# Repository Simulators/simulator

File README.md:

# simulator
The Liverpool Ringing Simulator Project

<b>The Type 1 simulator is no longer under active development. The repository for the Type 2 simulator is at https://github.com/Simulators/simulator-type2, and you should start there if you are building a new simulator.</b>

Here you will find archived all the resources for building the Liverpool Ringing Simulator Project's original (Type 1) simulator interfaces and sensor heads, including:
* Hardware & Software Manuals
* Firmware Source Code
* Eagle PCB Designs
* PCB Fabrication Gerber Files

If you didn't get here from http://www.simulators.org.uk/, you might want to go and look at that, too.

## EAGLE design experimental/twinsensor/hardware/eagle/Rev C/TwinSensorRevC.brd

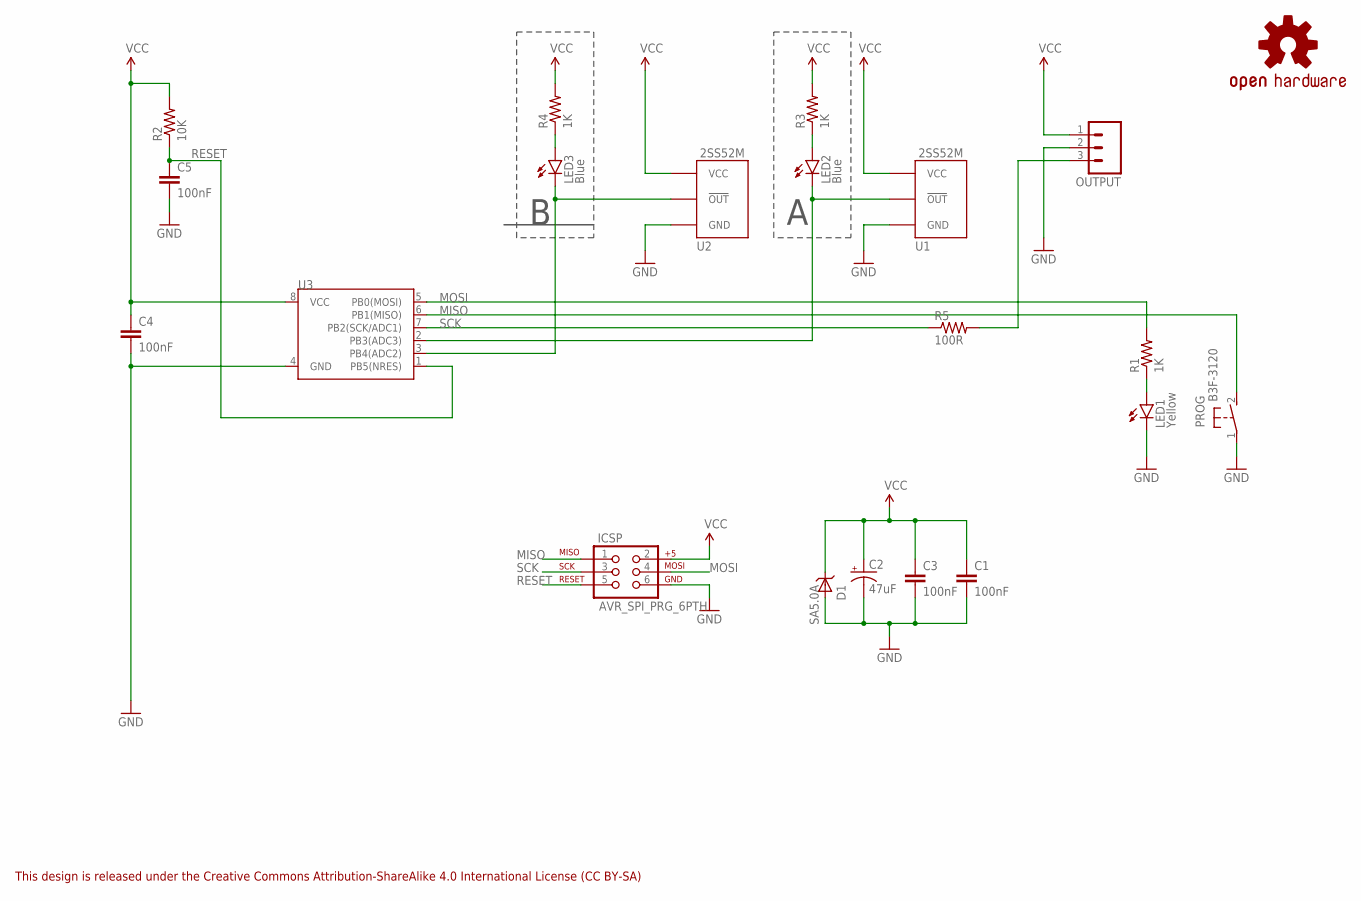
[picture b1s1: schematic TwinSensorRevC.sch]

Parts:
C1, C3, C4, C5: 100nF; CAP-PTH-SMALL
C2: 47uF; CPOL-RADIAL-100UF-25V
D1: SA5.0A; DO41_TVS_UNI
ICSP: AVR_SPI_PRG_6PTH; 2X3
LED1: Yellow; LED3MM
LED2, LED3: Blue; LED3MM
LOGO1: OSHW-LOGOS; OSHW-LOGO-S
OUTPUT: M03PTH; 1X03
PROG: B3F-3120
R1, R3, R4: 1K; AXIAL-0.4
R2: 10K; AXIAL-0.4
R5: 100R; AXIAL-0.4
U1, U2: 2SS52MVERT; 2SS52M_VERT
U3: ATTINY45DIL08_LONG_PADS; DIL08

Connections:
GND: C1.2, C2.2 (-), C3.2, C4.2, C5.2, D1.ANODE, ICSP.6, LED1.K (C), OUTPUT.2, PROG.1, U1.P$1 (GND), U2.P$1 (GND), U3.4 (GND)
MISO: ICSP.1, PROG.2 (S), U3.6 (PB1(MISO))
MOSI: ICSP.4, R1.P$2 (2), U3.5 (PB0(MOSI))
unnamed: LED2.A, R3.P$1 (1)
unnamed: LED3.A, R4.P$1 (1)
unnamed: LED1.A, R1.P$1 (1)
unnamed: LED2.K (C), U1.P$2 (!OUT!), U3.2 (PB3(ADC3))
unnamed: LED3.K (C), U2.P$2 (!OUT!), U3.3 (PB4(ADC2))
OUT: OUTPUT.3, R5.P$2 (2)
RESET: C5.1, ICSP.5, R2.P$1 (1), U3.1 (PB5(NRES))
SCK: ICSP.3, R5.P$1 (1), U3.7 (PB2(SCK/ADC1))
VCC: C1.1, C2.1 (+), C3.1, C4.1, D1.CATHODE, ICSP.2, OUTPUT.1, R2.P$2 (2), R3.P$2 (2), R4.P$2 (2), U1.P$3 (VCC), U2.P$3 (VCC), U3.8 (VCC)

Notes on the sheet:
This design is released under the Creative Commons Attribution-ShareAlike 4.0 International License (CC BY-SA)

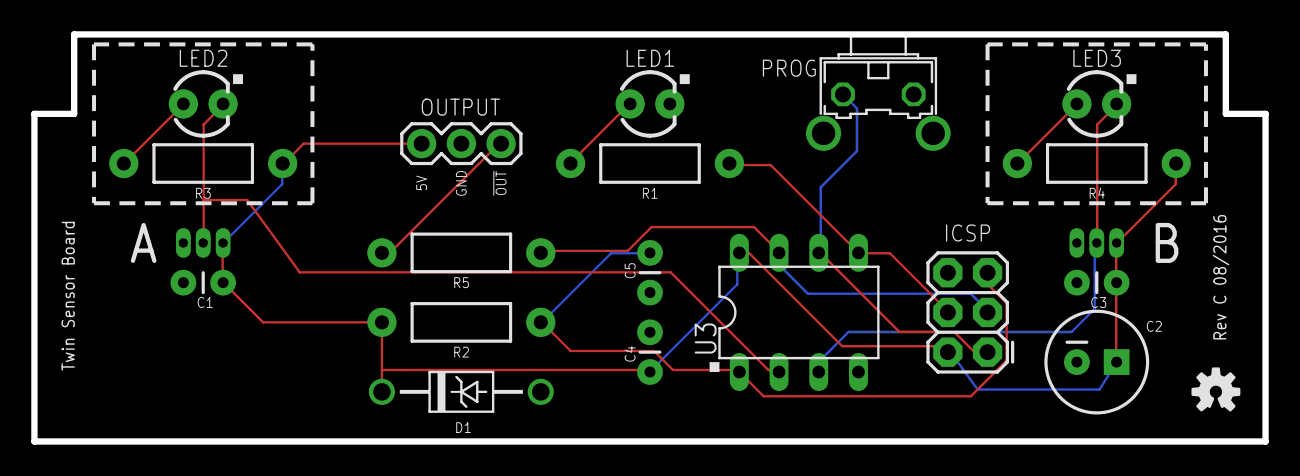
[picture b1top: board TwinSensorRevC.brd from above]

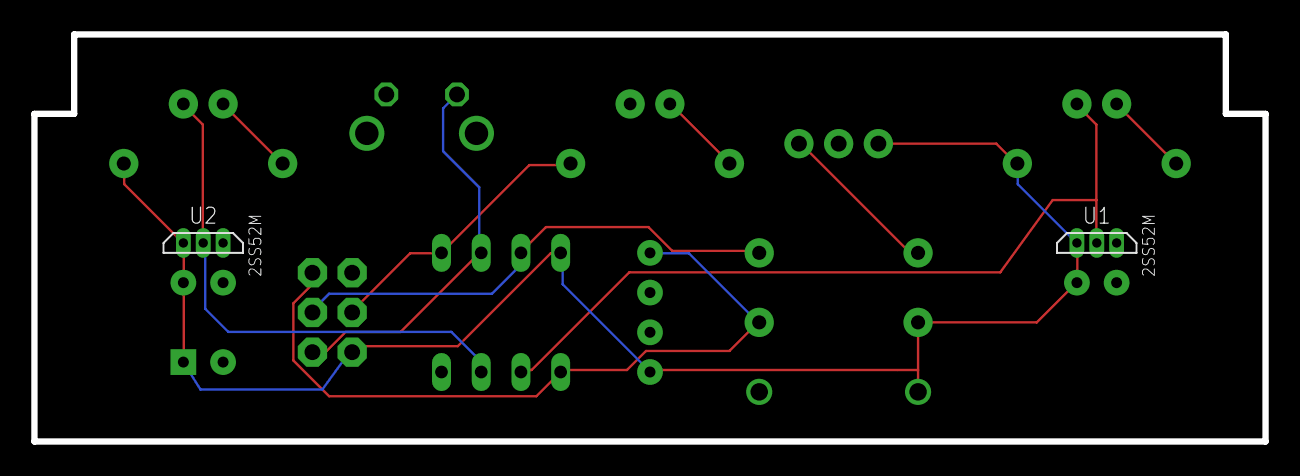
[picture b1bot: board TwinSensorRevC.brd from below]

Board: 2 copper layers, 78.7 x 26.0 mm, 21 parts (2 on the bottom side), 12 nets.

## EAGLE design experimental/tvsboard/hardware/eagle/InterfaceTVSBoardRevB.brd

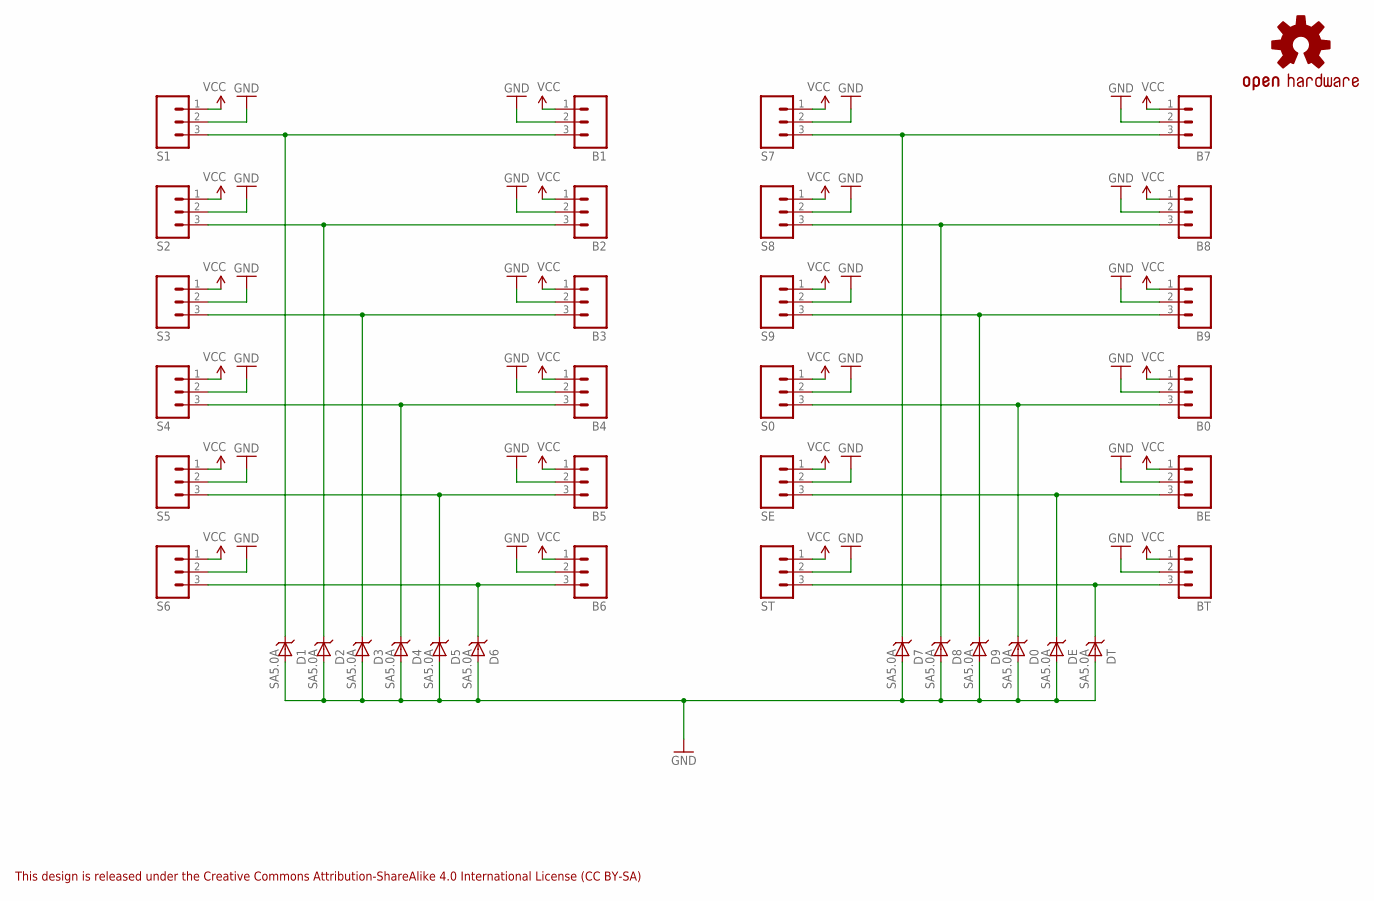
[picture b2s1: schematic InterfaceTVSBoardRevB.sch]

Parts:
B0, B1, B2, B3, B4, B5, B6, B7, B8, B9: M03PTH; 1X03
BE: M03PTH; 1X03
BT: M03PTH; 1X03
D0, D1, D2, D3, D4, D5, D6, D7, D8, D9: SA5.0A; DO41_TVS_UNI
DE: SA5.0A; DO41_TVS_UNI
DT: SA5.0A; DO41_TVS_UNI
LOGO1: OSHW-LOGOS; OSHW-LOGO-S
S0, S1, S2, S3, S4, S5, S6, S7, S8, S9: M03PTH; 1X03
SE: M03PTH; 1X03
ST: M03PTH; 1X03

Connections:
GND: B0.2, B1.2, B2.2, B3.2, B4.2, B5.2, B6.2, B7.2, B8.2, B9.2, BE.2, BT.2, D0.ANODE, D1.ANODE, D2.ANODE, D3.ANODE, D4.ANODE, D5.ANODE, D6.ANODE, D7.ANODE, D8.ANODE, D9.ANODE, DE.ANODE, DT.ANODE, S0.2, S1.2, S2.2, S3.2, S4.2, S5.2, S6.2, S7.2, S8.2, S9.2, SE.2, ST.2
unnamed: B1.3, D1.CATHODE, S1.3
unnamed: B2.3, D2.CATHODE, S2.3
unnamed: B3.3, D3.CATHODE, S3.3
unnamed: B4.3, D4.CATHODE, S4.3
unnamed: B5.3, D5.CATHODE, S5.3
unnamed: B6.3, D6.CATHODE, S6.3
unnamed: B7.3, D7.CATHODE, S7.3
unnamed: B8.3, D8.CATHODE, S8.3
unnamed: B9.3, D9.CATHODE, S9.3
unnamed: B0.3, D0.CATHODE, S0.3
unnamed: BE.3, DE.CATHODE, SE.3
unnamed: BT.3, DT.CATHODE, ST.3
VCC: B0.1, B1.1, B2.1, B3.1, B4.1, B5.1, B6.1, B7.1, B8.1, B9.1, BE.1, BT.1, S0.1, S1.1, S2.1, S3.1, S4.1, S5.1, S6.1, S7.1, S8.1, S9.1, SE.1, ST.1

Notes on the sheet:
This design is released under the Creative Commons Attribution-ShareAlike 4.0 International License (CC BY-SA)

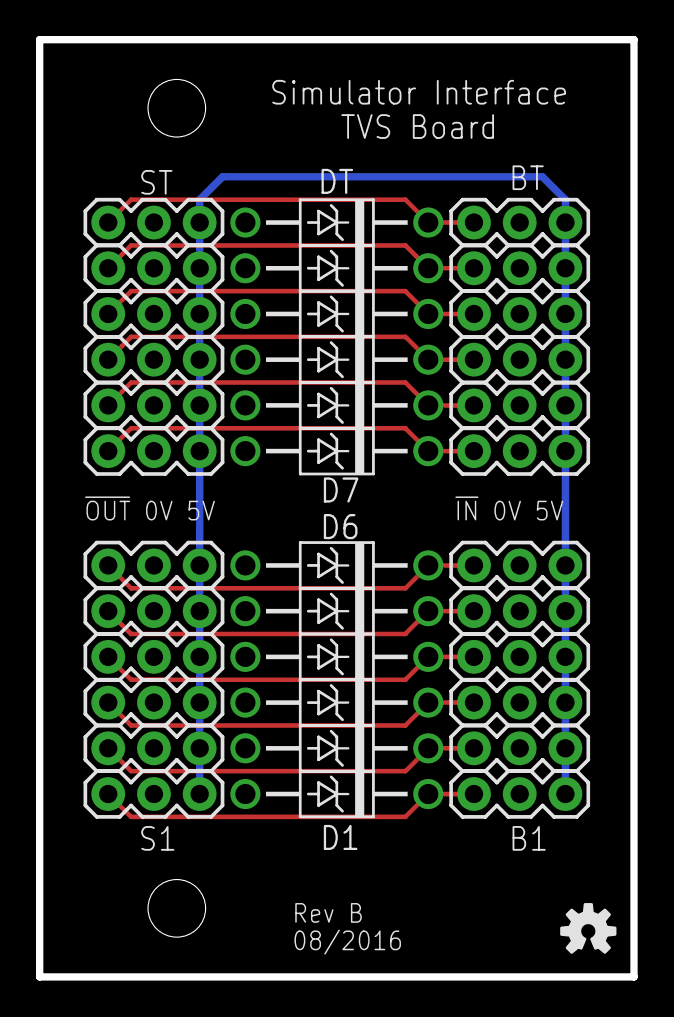
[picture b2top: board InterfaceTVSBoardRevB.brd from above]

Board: 2 copper layers, 33.0 x 52.1 mm, 37 parts (0 on the bottom side), 14 nets.

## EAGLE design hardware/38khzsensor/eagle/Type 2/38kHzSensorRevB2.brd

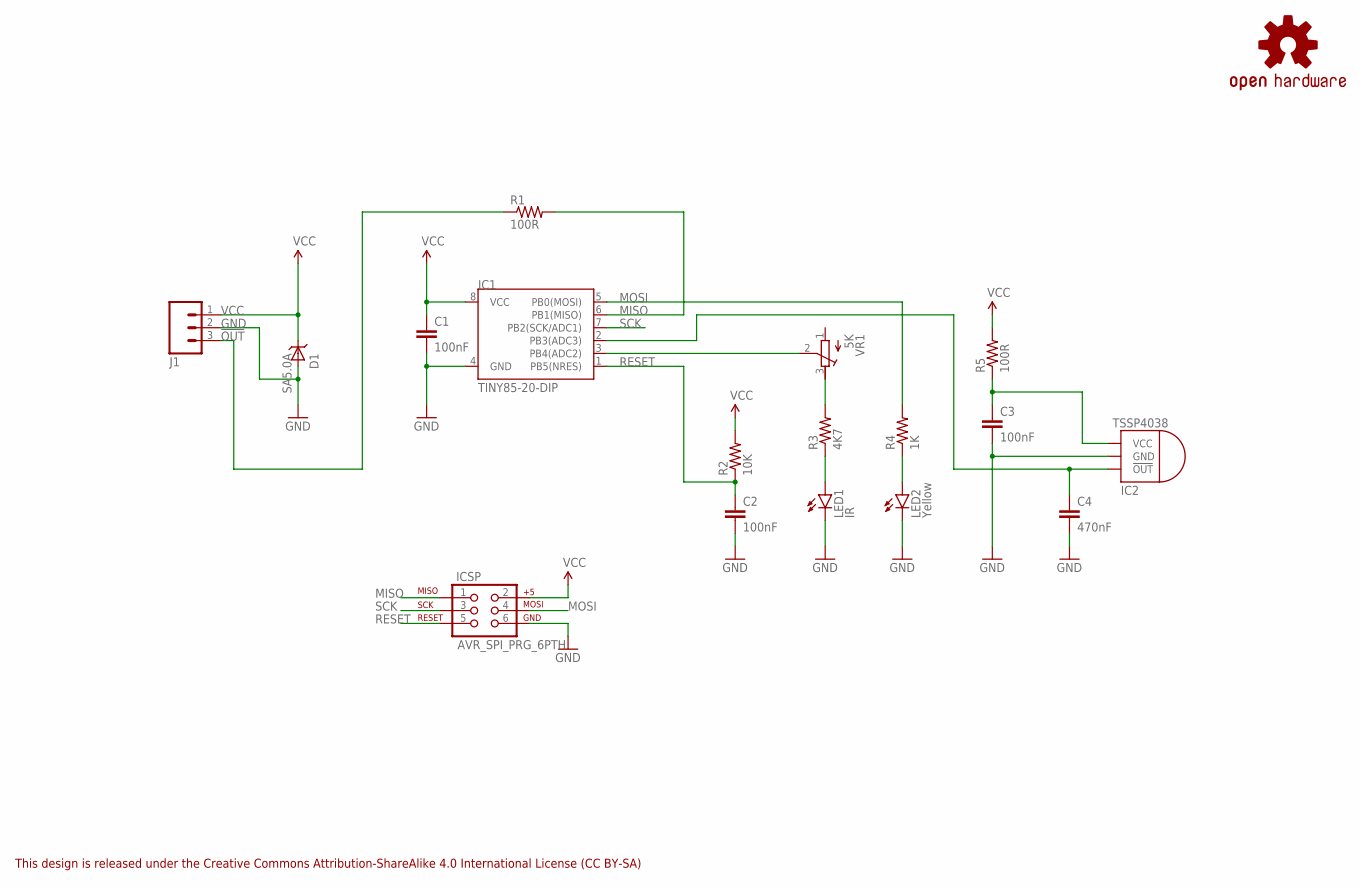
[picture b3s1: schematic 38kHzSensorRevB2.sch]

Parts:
C1, C2, C3: 100nF; CAP-PTH-SMALL
C4: 470nF; CAP-PTH-5MM
D1: SA5.0A; DO41_TVS_UNI
IC1: TINY85-20-DIP; DIP08
IC2: TSSP4038EDGE; TSSP4038_PKG_EDGE
ICSP: AVR_SPI_PRG_6PTH; 2X3
J1: M03PTH; 1X03
LED1: IR; LED5MM
LED2: Yellow; LED3MM
LOGO1: OSHW-LOGOS; OSHW-LOGO-S
R1, R5: 100R; AXIAL-0.4
R2: 10K; AXIAL-0.4
R3: 4K7; AXIAL-0.4
R4: 1K; AXIAL-0.4
VR1: 5K; RTRIM3296X

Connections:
!OUT: J1.3, R1.P$1 (1)
GND: C1.2, C2.2, C3.2, C4.2, D1.ANODE, IC1.4 (GND), IC2.GND, ICSP.6, J1.2, LED1.K (C), LED2.K (C)
MISO: IC1.6 (PB1(MISO)), ICSP.1, R1.P$2 (2)
MOSI: IC1.5 (PB0(MOSI)), ICSP.4, R4.P$2 (2)
unnamed: IC1.3 (PB4(ADC2)), VR1.2 (S)
unnamed: R3.P$2 (2), VR1.3 (E)
unnamed: C4.1, IC1.2 (PB3(ADC3)), IC2.OUT (!OUT)
unnamed: C3.1, IC2.VCC, R5.P$1 (1)
unnamed: LED1.A, R3.P$1 (1)
unnamed: LED2.A, R4.P$1 (1)
RESET: C2.1, IC1.1 (PB5(NRES)), ICSP.5, R2.P$1 (1)
SCK: IC1.7 (PB2(SCK/ADC1)), ICSP.3
VCC: C1.1, D1.CATHODE, IC1.8 (VCC), ICSP.2, J1.1, R2.P$2 (2), R5.P$2 (2)

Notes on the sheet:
This design is released under the Creative Commons Attribution-ShareAlike 4.0 International License (CC BY-SA)

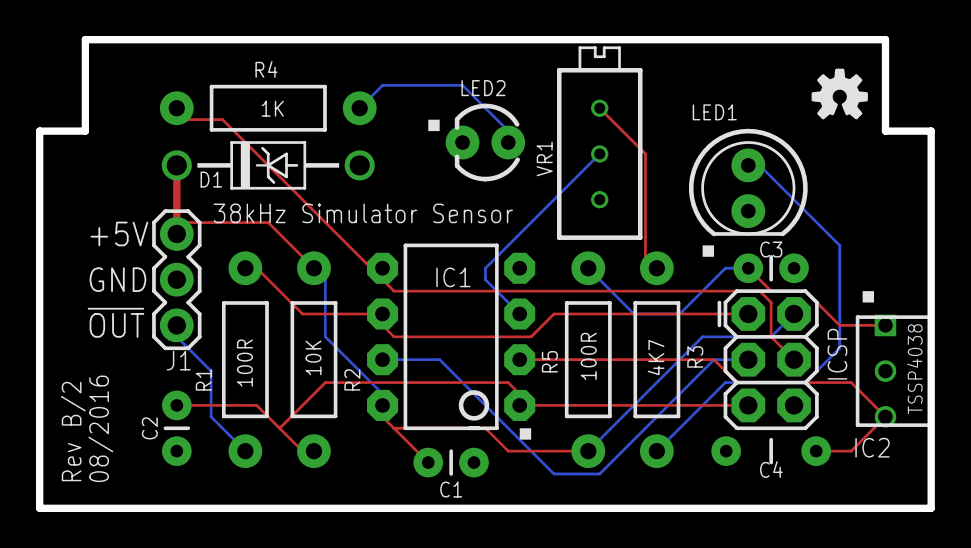
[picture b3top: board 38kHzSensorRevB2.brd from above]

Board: 2 copper layers, 49.5 x 26.0 mm, 18 parts (0 on the bottom side), 13 nets.

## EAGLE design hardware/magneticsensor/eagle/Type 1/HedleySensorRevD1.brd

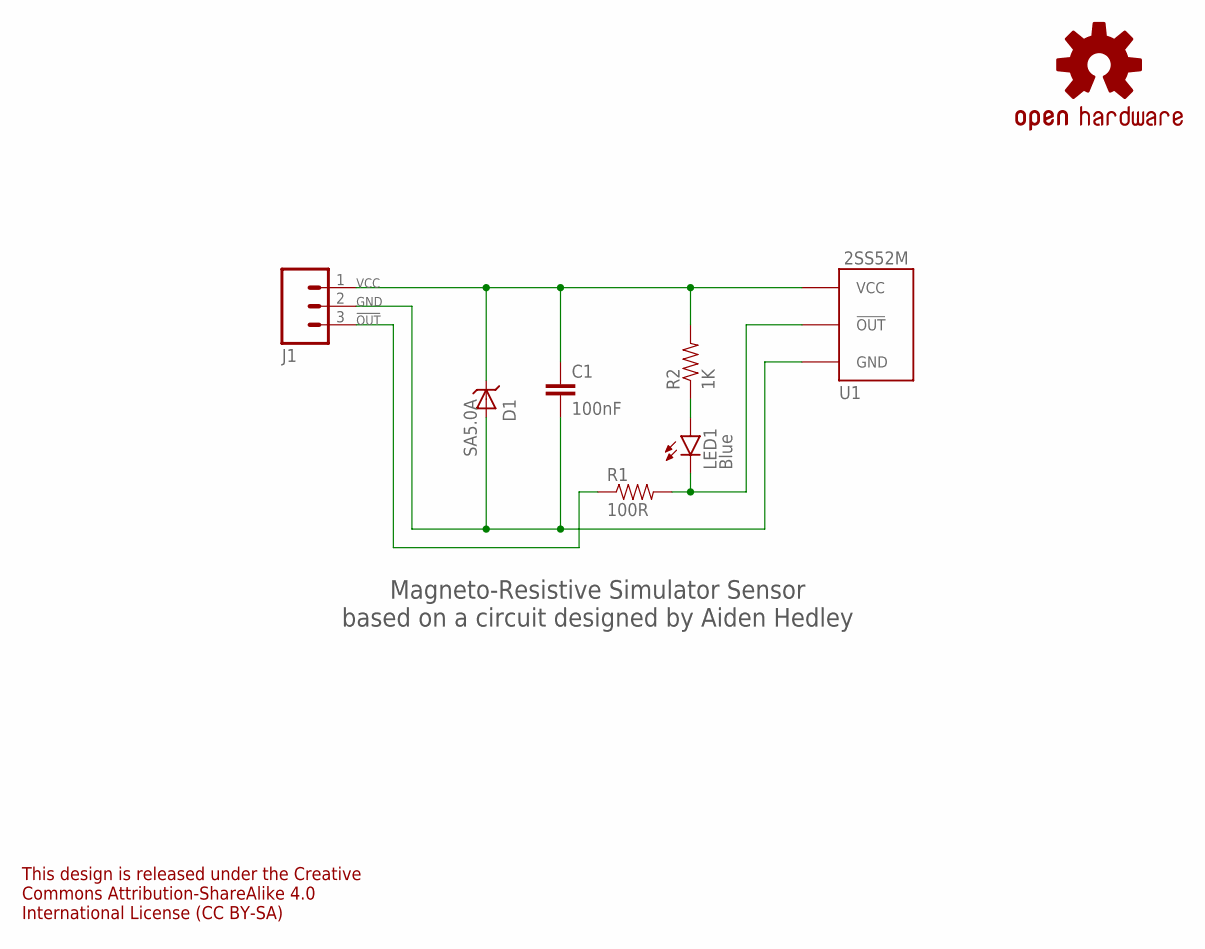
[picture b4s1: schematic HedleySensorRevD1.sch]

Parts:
C1: 100nF; CAP-PTH-SMALL
D1: SA5.0A; DO41_TVS_UNI
J1: M03PTH; 1X03
LED1: Blue; LED3MM
LOGO1: OSHW-LOGOS; OSHW-LOGO-S
R1: 100R; AXIAL-0.4
R2: 1K; AXIAL-0.4
U1: 2SS52MFLAT; 2SS52M_FLAT

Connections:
!OUT: J1.3, R1.P$1 (1)
GND: C1.2, D1.ANODE, J1.2, U1.P$1 (GND)
unnamed: LED1.K (C), R1.P$2 (2), U1.P$2 (!OUT!)
unnamed: LED1.A, R2.P$1 (1)
VCC: C1.1, D1.CATHODE, J1.1, R2.P$2 (2), U1.P$3 (VCC)

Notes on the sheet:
Magneto-Resistive Simulator Sensor based on a circuit designed by Aiden Hedley
This design is released under the Creative Commons Attribution-ShareAlike 4.0 International License (CC BY-SA)

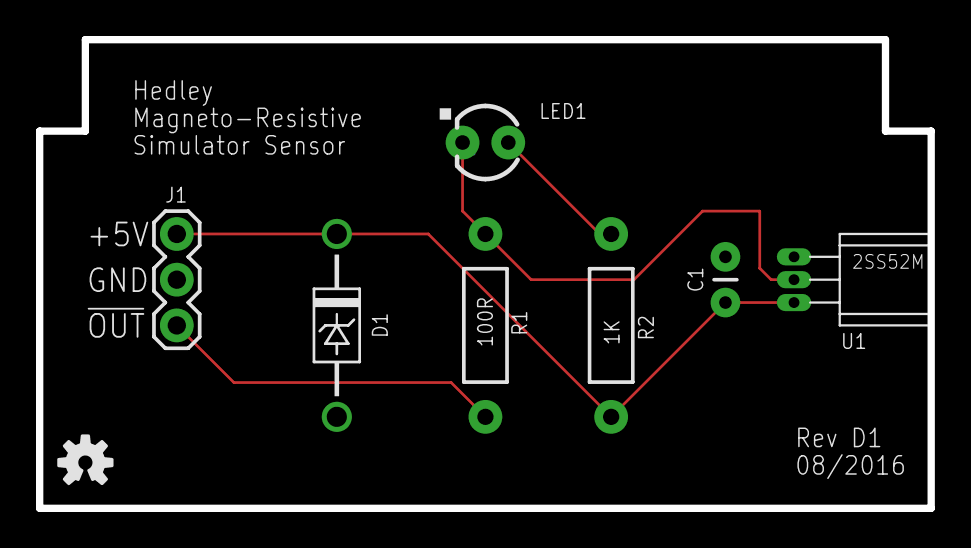
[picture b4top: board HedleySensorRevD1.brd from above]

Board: 2 copper layers, 49.5 x 26.0 mm, 8 parts (0 on the bottom side), 5 nets.

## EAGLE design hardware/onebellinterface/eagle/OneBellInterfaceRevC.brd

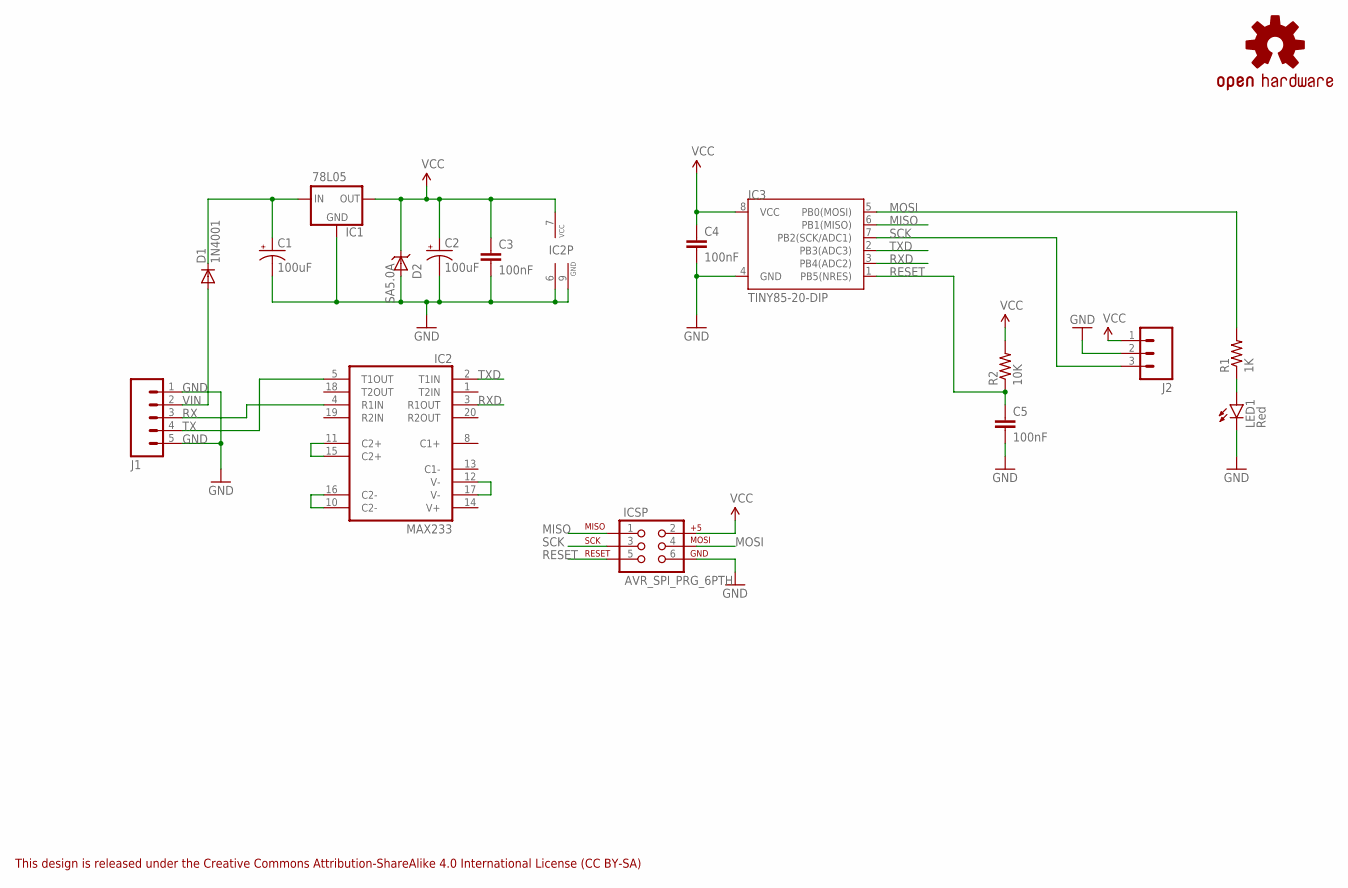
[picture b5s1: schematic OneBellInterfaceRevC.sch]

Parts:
C1, C2: 100uF; CPOL-RADIAL-100UF-25V
C3, C4, C5: 100nF; CAP-PTH-SMALL
D1: 1N4001; DO41_DIODE
D2: SA5.0A; DO41_TVS_UNI
IC1: 78L05; TO-92
IC2: MAX233; DIL20
IC3: TINY85-20-DIP; DIL08
ICSP: AVR_SPI_PRG_6PTH; 2X3
J1: M05PTH; 1X05
J2: M03PTH; 1X03
LED1: Red; LED3MM
LOGO1: OSHW-LOGOS; OSHW-LOGO-S
R1: 1K; AXIAL-0.4
R2: 10K; AXIAL-0.4

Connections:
GND: C1.2 (-), C2.2 (-), C3.2, C4.2, C5.2, D2.ANODE, IC1.2 (GND), IC2.6 (GND), IC2.9 (GND), IC3.4 (GND), ICSP.6, J1.1, J1.5, J2.2, LED1.K (C)
MISO: IC3.6 (PB1(MISO)), ICSP.1
MOSI: IC3.5 (PB0(MOSI)), ICSP.4, R1.P$2 (2)
unnamed: C1.1 (+), D1.C, IC1.3 (IN)
unnamed: LED1.A, R1.P$1 (1)
unnamed: IC2.11 (C2+), IC2.15 (C2+)
unnamed: IC2.10 (C2-), IC2.16 (C2-)
unnamed: IC2.12 (V-), IC2.17 (V-)
RESET: C5.1, IC3.1 (PB5(NRES)), ICSP.5, R2.P$1 (1)
RX: IC2.4 (R1IN), J1.3
RXD: IC2.3 (R1OUT), IC3.3 (PB4(ADC2))
SCK: IC3.7 (PB2(SCK/ADC1)), ICSP.3, J2.3
TX: IC2.5 (T1OUT), J1.4
TXD: IC2.2 (T1IN), IC3.2 (PB3(ADC3))
VCC: C2.1 (+), C3.1, C4.1, D2.CATHODE, IC1.1 (OUT), IC2.7 (VCC), IC3.8 (VCC), ICSP.2, J2.1, R2.P$2 (2)
VIN: D1.A, J1.2

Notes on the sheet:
This design is released under the Creative Commons Attribution-ShareAlike 4.0 International License (CC BY-SA)

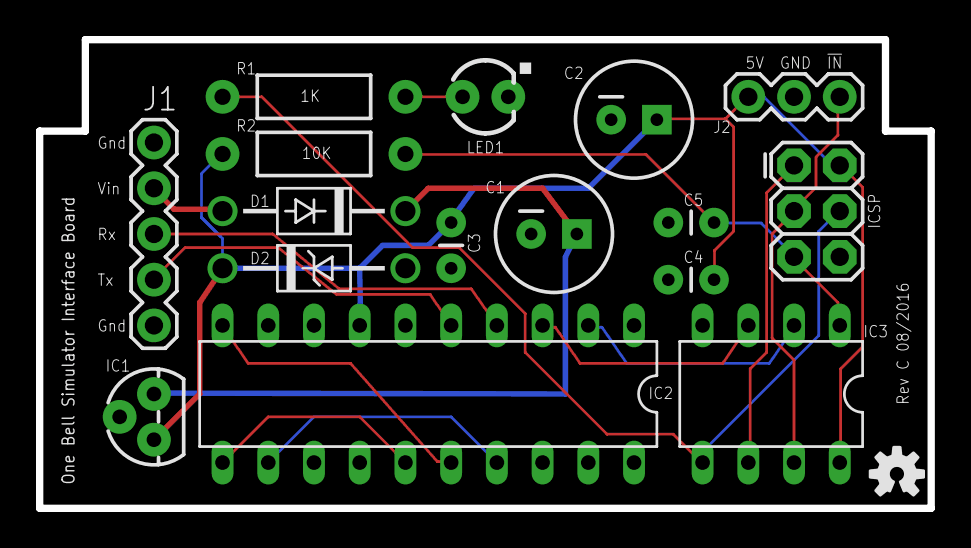
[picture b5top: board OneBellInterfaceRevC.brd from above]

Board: 2 copper layers, 49.5 x 26.0 mm, 17 parts (0 on the bottom side), 16 nets.

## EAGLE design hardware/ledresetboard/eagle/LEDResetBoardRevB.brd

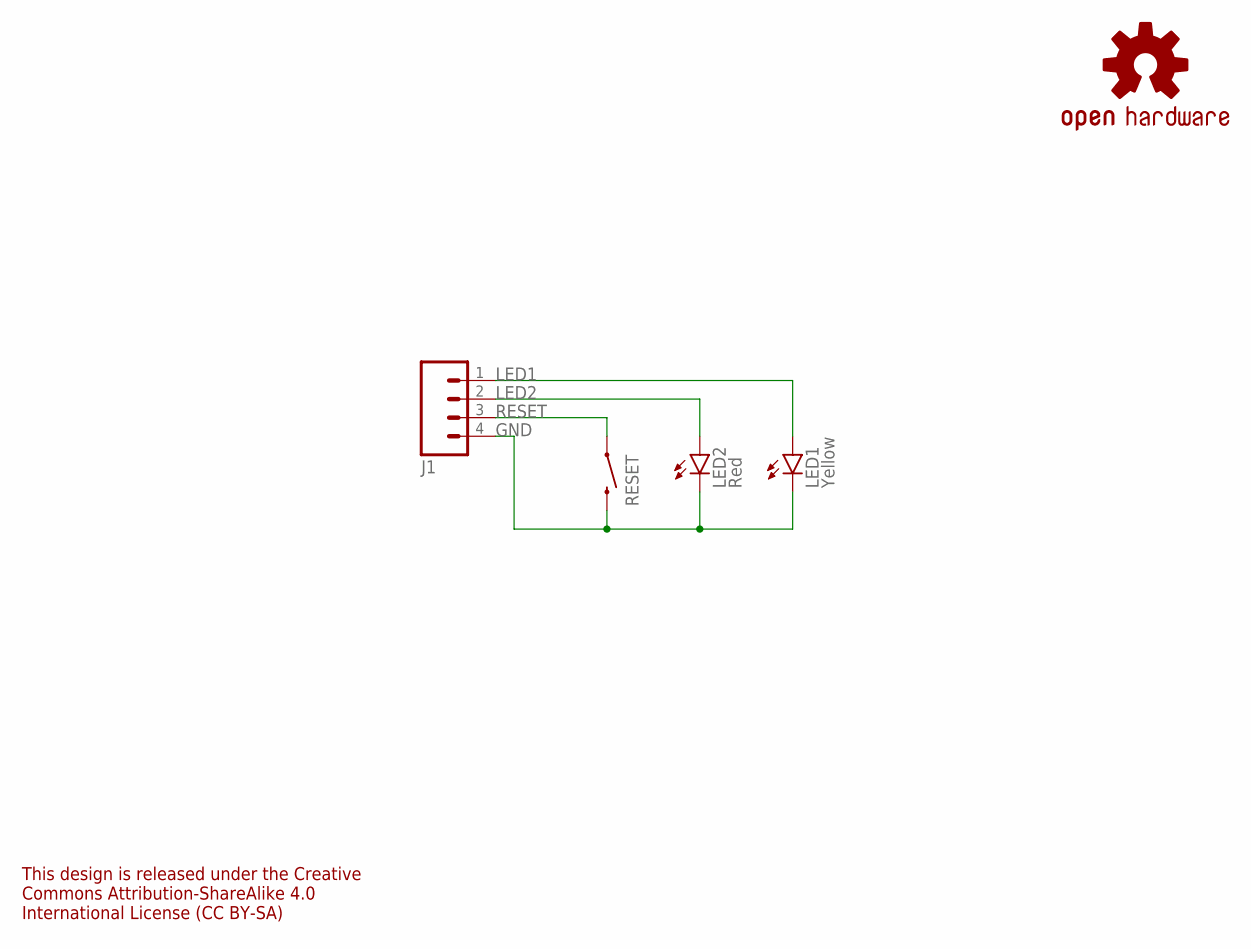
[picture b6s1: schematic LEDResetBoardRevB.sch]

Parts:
J1: M04PTH; 1X04
LED1: Yellow; LED3MM
LED2: Red; LED3MM
LOGO1: OSHW-LOGOS; OSHW-LOGO-S
RESET: SWITCH-MOMENTARY-2PTH; TACTILE-PTH

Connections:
GND: J1.4, LED1.K (C), LED2.K (C), RESET.3 (2)
LED1: J1.1, LED1.A
LED2: J1.2, LED2.A
RESET: J1.3, RESET.1

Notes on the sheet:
This design is released under the Creative Commons Attribution-ShareAlike 4.0 International License (CC BY-SA)

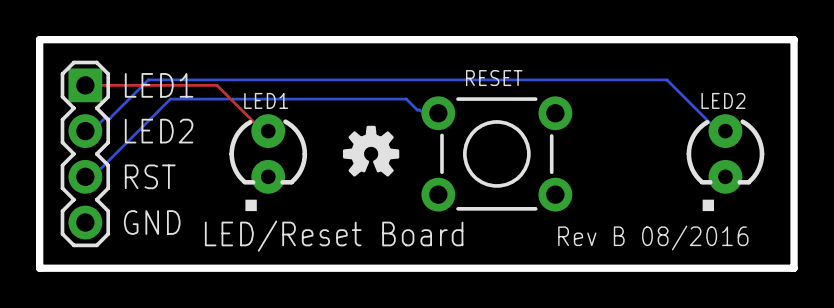
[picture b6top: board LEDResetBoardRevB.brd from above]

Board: 2 copper layers, 41.9 x 12.7 mm, 5 parts (0 on the bottom side), 4 nets.

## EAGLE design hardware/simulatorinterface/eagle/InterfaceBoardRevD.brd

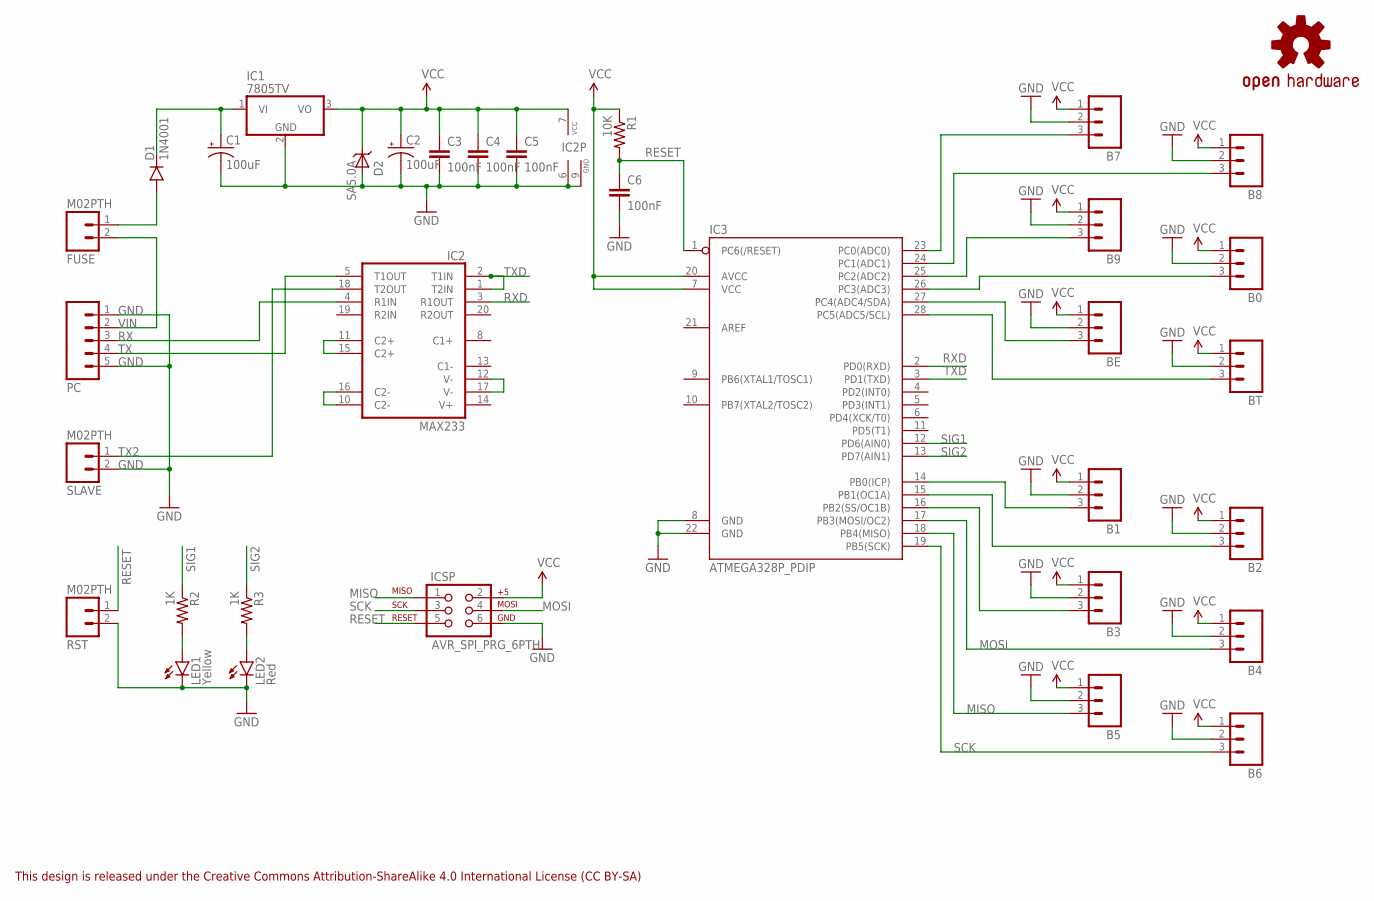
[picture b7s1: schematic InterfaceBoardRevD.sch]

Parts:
B0, B1, B2, B3, B4, B5, B6, B7, B8, B9: M03PTH; 1X03
BE: M03PTH; 1X03
BT: M03PTH; 1X03
C1, C2: 100uF; CPOL-RADIAL-100UF-25V
C3, C4, C5, C6: 100nF; CAP-PTH-SMALL
D1: 1N4001; DO41_DIODE
D2: SA5.0A; DO41_TVS_UNI
FUSE: M02PTH; 1X02
IC1: 7805TV; TO220V
IC2: MAX233; DIL20
IC3: ATMEGA328P_PDIP; DIL28-3
ICSP: AVR_SPI_PRG_6PTH; 2X3
LED1: Yellow; LED3MM_LARGEHOLES
LED2: Red; LED3MM_LARGEHOLES
LOGO1: OSHW-LOGOS; OSHW-LOGO-S
PC: M05PTH; 1X05
R1: 10K; AXIAL-0.4
R2, R3: 1K; AXIAL-0.4
RST: M02PTH; 1X02
SLAVE: M02PTH; 1X02

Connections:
GND: B0.2, B1.2, B2.2, B3.2, B4.2, B5.2, B6.2, B7.2, B8.2, B9.2, BE.2, BT.2, C1.2 (-), C2.2 (-), C3.2, C4.2, C5.2, C6.2, D2.ANODE, IC1.2 (GND), IC2.6 (GND), IC2.9 (GND), IC3.8 (GND), IC3.22 (GND), ICSP.6, LED1.K (C), LED2.K (C), PC.1, PC.5, RST.2, SLAVE.2
MISO: B5.3, IC3.18 (PB4(MISO)), ICSP.1
MOSI: B4.3, IC3.17 (PB3(MOSI/OC2)), ICSP.4
unnamed: B7.3, IC3.23 (PC0(ADC0))
unnamed: B8.3, IC3.24 (PC1(ADC1))
unnamed: B9.3, IC3.25 (PC2(ADC2))
unnamed: B0.3, IC3.26 (PC3(ADC3))
unnamed: BT.3, IC3.28 (PC5(ADC5/SCL))
unnamed: BE.3, IC3.27 (PC4(ADC4/SDA))
unnamed: LED1.A, R2.P$2 (2)
unnamed: IC2.10 (C2-), IC2.16 (C2-)
unnamed: B3.3, IC3.16 (PB2(SS/OC1B))
unnamed: B2.3, IC3.15 (PB1(OC1A))
unnamed: B1.3, IC3.14 (PB0(ICP))
unnamed: IC2.11 (C2+), IC2.15 (C2+)
unnamed: IC2.12 (V-), IC2.17 (V-)
unnamed: D1.A, FUSE.1
unnamed: LED2.A, R3.P$2 (2)
unnamed: C1.1 (+), D1.C, IC1.1 (VI)
RESET: C6.1, IC3.1 (PC6(/RESET)), ICSP.5, R1.P$2 (2), RST.1
RX: IC2.4 (R1IN), PC.3
RXD: IC2.3 (R1OUT), IC3.2 (PD0(RXD))
SCK: B6.3, IC3.19 (PB5(SCK)), ICSP.3
SIG1: IC3.12 (PD6(AIN0)), R2.P$1 (1)
SIG2: IC3.13 (PD7(AIN1)), R3.P$1 (1)
TX: IC2.5 (T1OUT), PC.4
TX2: IC2.18 (T2OUT), SLAVE.1
TXD: IC2.1 (T2IN), IC2.2 (T1IN), IC3.3 (PD1(TXD))
VCC: B0.1, B1.1, B2.1, B3.1, B4.1, B5.1, B6.1, B7.1, B8.1, B9.1, BE.1, BT.1, C2.1 (+), C3.1, C4.1, C5.1, D2.CATHODE, IC1.3 (VO), IC2.7 (VCC), IC3.7 (VCC), IC3.20 (AVCC), ICSP.2, R1.P$1 (1)
VIN: FUSE.2, PC.2

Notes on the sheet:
This design is released under the Creative Commons Attribution-ShareAlike 4.0 International License (CC BY-SA)

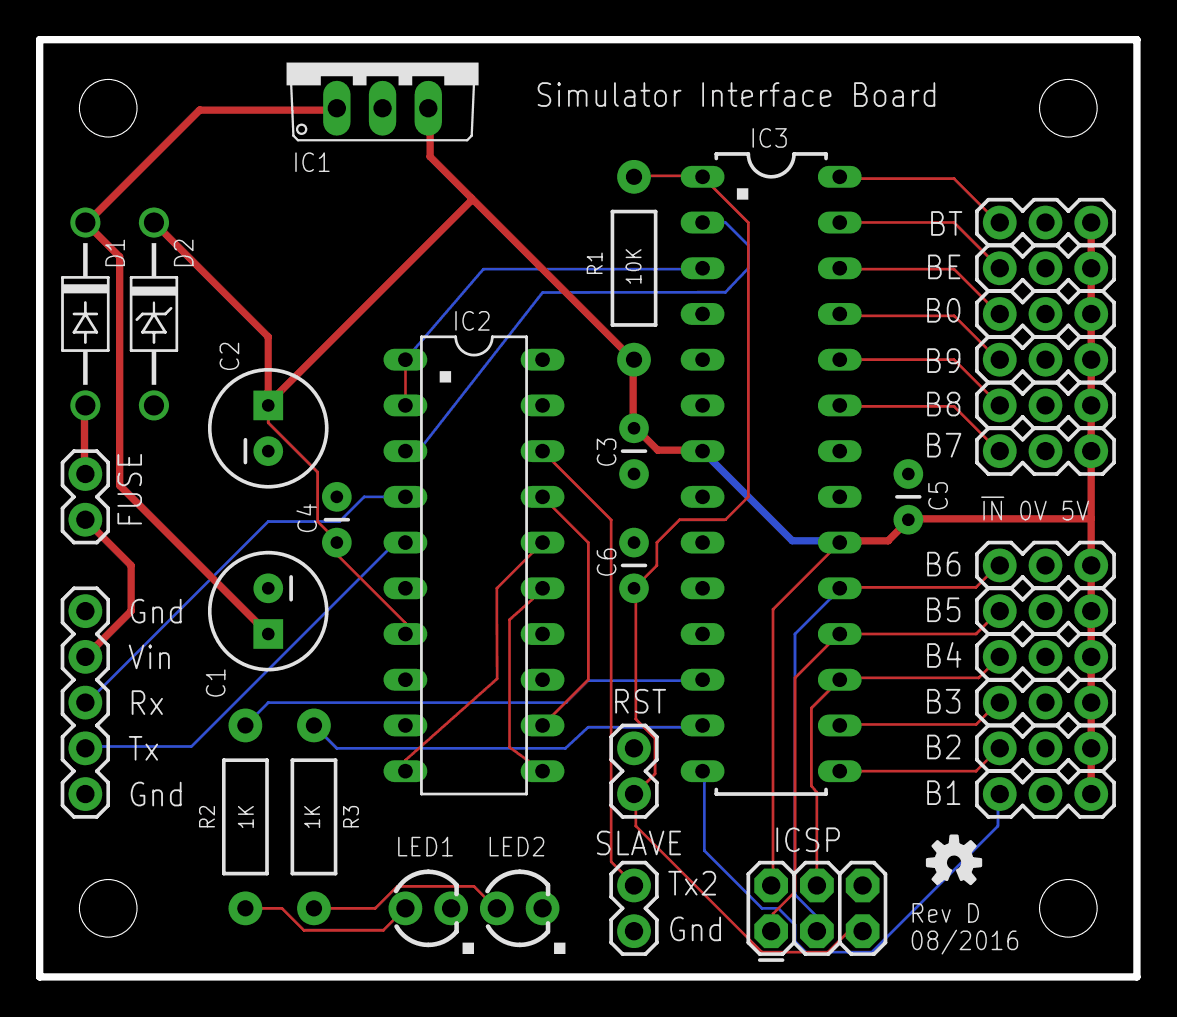
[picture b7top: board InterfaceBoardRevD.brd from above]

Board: 2 copper layers, 61.0 x 52.1 mm, 34 parts (0 on the bottom side), 30 nets.

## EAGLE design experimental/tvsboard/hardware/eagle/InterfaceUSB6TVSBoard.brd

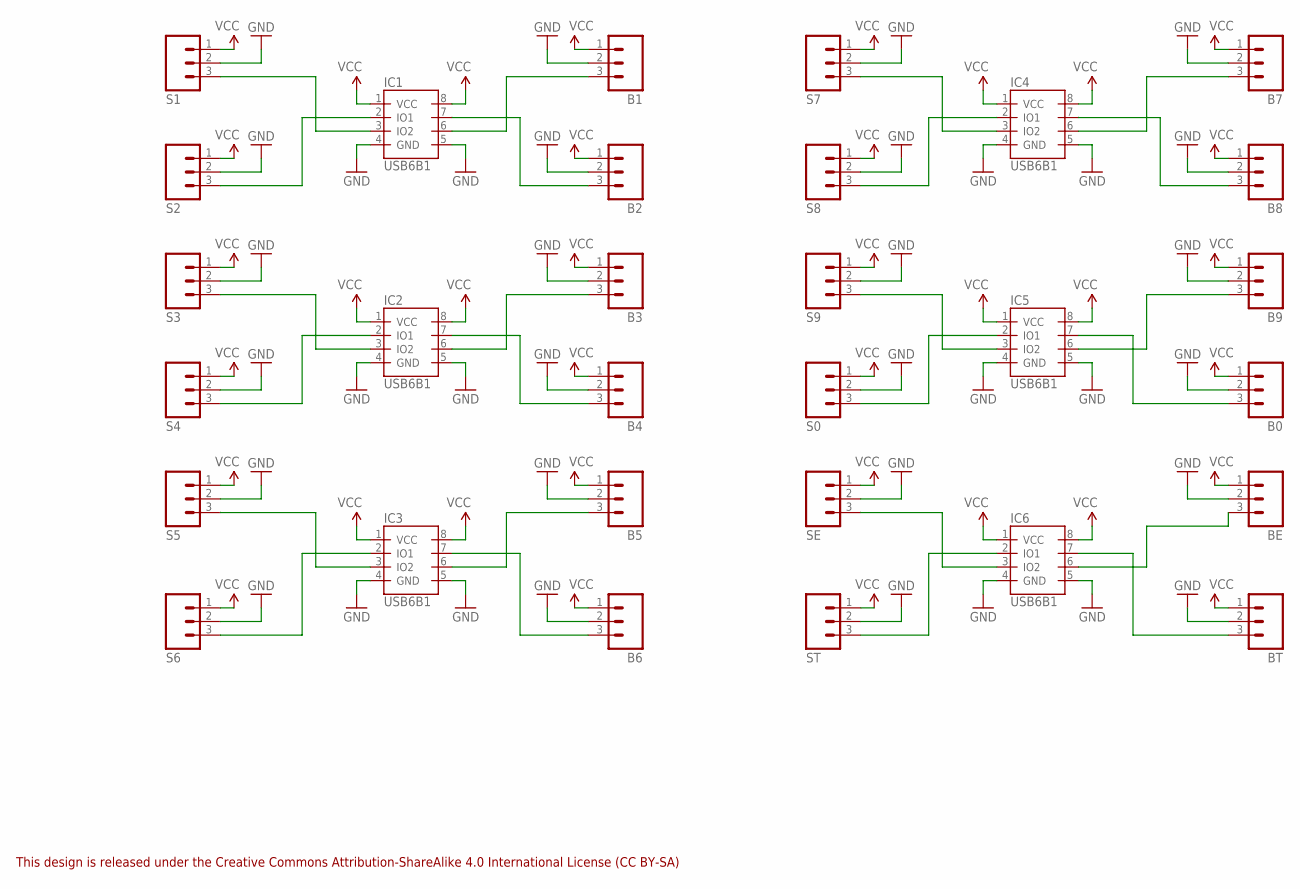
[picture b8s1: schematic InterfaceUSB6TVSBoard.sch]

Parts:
B0, B1, B2, B3, B4, B5, B6, B7, B8, B9: M03PTH; 1X03
BE: M03PTH; 1X03
BT: M03PTH; 1X03
IC1, IC2, IC3, IC4, IC5, IC6: USB6B1; SO08
S0, S1, S2, S3, S4, S5, S6, S7, S8, S9: M03PTH; 1X03
SE: M03PTH; 1X03
ST: M03PTH; 1X03

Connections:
GND: B0.2, B1.2, B2.2, B3.2, B4.2, B5.2, B6.2, B7.2, B8.2, B9.2, BE.2, BT.2, IC1.4 (GND), IC1.5 (GND), IC2.4 (GND), IC2.5 (GND), IC3.4 (GND), IC3.5 (GND), IC4.4 (GND), IC4.5 (GND), IC5.4 (GND), IC5.5 (GND), IC6.4 (GND), IC6.5 (GND), S0.2, S1.2, S2.2, S3.2, S4.2, S5.2, S6.2, S7.2, S8.2, S9.2, SE.2, ST.2
unnamed: IC1.3 (IO2), S1.3
unnamed: IC1.2 (IO1), S2.3
unnamed: B1.3, IC1.6 (IO2)
unnamed: B2.3, IC1.7 (IO1)
unnamed: IC2.3 (IO2), S3.3
unnamed: B3.3, IC2.6 (IO2)
unnamed: IC2.2 (IO1), S4.3
unnamed: B4.3, IC2.7 (IO1)
unnamed: IC3.3 (IO2), S5.3
unnamed: B5.3, IC3.6 (IO2)
unnamed: IC3.2 (IO1), S6.3
unnamed: B6.3, IC3.7 (IO1)
unnamed: IC4.3 (IO2), S7.3
unnamed: IC4.2 (IO1), S8.3
unnamed: IC5.3 (IO2), S9.3
unnamed: B9.3, IC5.6 (IO2)
unnamed: IC6.3 (IO2), SE.3
unnamed: BE.3, IC6.6 (IO2)
unnamed: B8.3, IC4.7 (IO1)
unnamed: B7.3, IC4.6 (IO2)
unnamed: IC6.2 (IO1), ST.3
unnamed: BT.3, IC6.7 (IO1)
unnamed: IC5.2 (IO1), S0.3
unnamed: B0.3, IC5.7 (IO1)
VCC: B0.1, B1.1, B2.1, B3.1, B4.1, B5.1, B6.1, B7.1, B8.1, B9.1, BE.1, BT.1, IC1.1 (VCC), IC1.8 (VCC), IC2.1 (VCC), IC2.8 (VCC), IC3.1 (VCC), IC3.8 (VCC), IC4.1 (VCC), IC4.8 (VCC), IC5.1 (VCC), IC5.8 (VCC), IC6.1 (VCC), IC6.8 (VCC), S0.1, S1.1, S2.1, S3.1, S4.1, S5.1, S6.1, S7.1, S8.1, S9.1, SE.1, ST.1

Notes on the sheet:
This design is released under the Creative Commons Attribution-ShareAlike 4.0 International License (CC BY-SA)

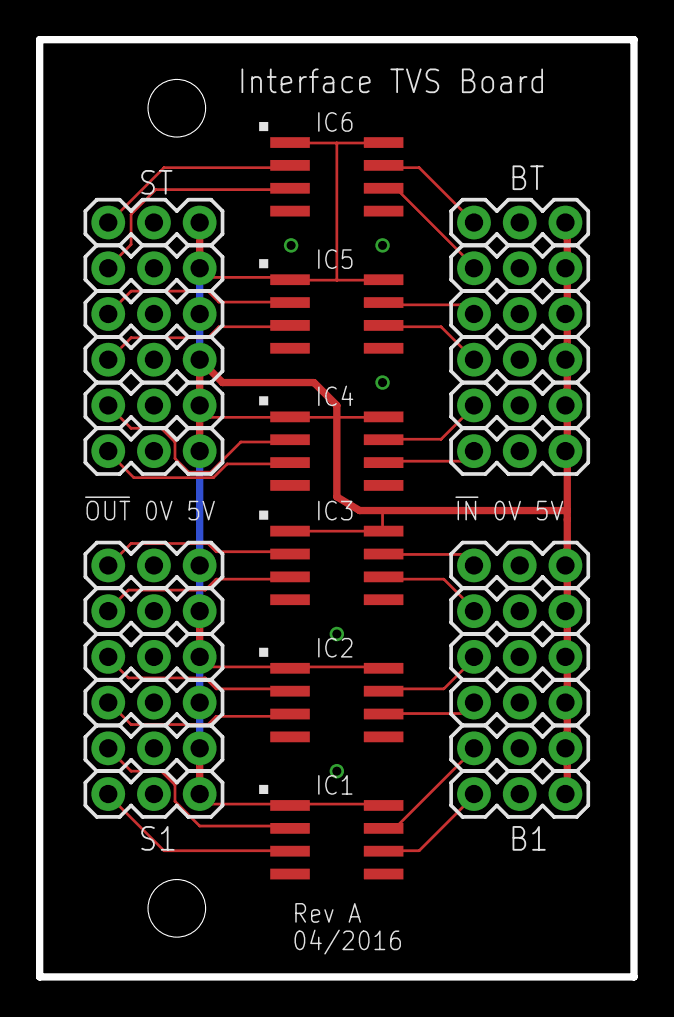
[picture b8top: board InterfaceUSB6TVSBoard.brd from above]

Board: 2 copper layers, 33.0 x 52.1 mm, 30 parts (0 on the bottom side), 26 nets.

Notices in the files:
parts and their libraries:
SparkFun-Connectors: Licensing: Creative Commons ShareAlike 4.0 International - https://creativecommons.org/licenses/by-sa/4.0
